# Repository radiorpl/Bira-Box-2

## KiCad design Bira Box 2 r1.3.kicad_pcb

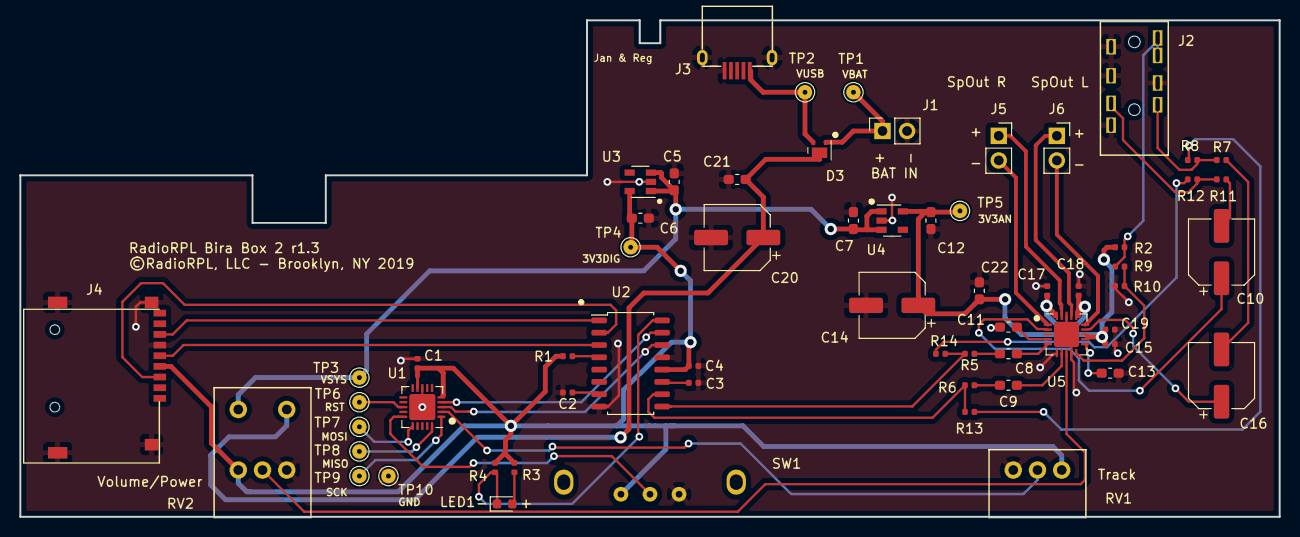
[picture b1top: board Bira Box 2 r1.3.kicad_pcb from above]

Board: 2 copper layers, 130.0 x 51.3 mm, 62 parts (1 on the bottom side), 45 nets.

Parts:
C1, C2, C3, C4, C15, C17, C18, C19: 0.1 uF; C_0402_1005Metric
C5, C6, C7, C8, C9, C12, C13: 1 uF; C_0603_1608Metric_Pad1.05x0.95mm_HandSolder
C10, C16: 220 uF; CP_Elec_6.3x5.8
C11, C21: 2.2 uF; C_0603_1608Metric_Pad1.05x0.95mm_HandSolder
C14: 100 uF; CP_Elec_6.3x5.8
C20: 22 uF; CP_Elec_6.3x5.8
C22: 10 uF; C_0603_1608Metric_Pad1.05x0.95mm_HandSolder
D3: PMEG2020CPA; HUSON-3-1EP_2x2mm_P1.3mm_EP1.1x1.6mm
J1, J5, J6: Conn_01x02_Female; PinSocket_1x02_P2.54mm_Vertical
J2: AudioJack3_SwitchTR; PJ-3930-8A
J3: USB_B_Micro; Korean-hropartsC145779
J4: Micro_SD_Card; microSD_TF01A
LED1: PLAY; LED_0603_1608Metric
R1: 22K; C_0402_1005Metric
R2: 10k; C_0402_1005Metric
R3: 2.2K; C_0402_1005Metric
R4: 10K; C_0402_1005Metric
R5, R6: 162K; C_0402_1005Metric
R7, R8, R9, R10, R11, R12, R13, R14: 0; C_0402_1005Metric
RV1: 10K; TT_PO91
RV2: 50K; TT_P091S
SW1: SW_SPDT; Alps_SSSU111400
TP1, TP2, TP3, TP4, TP5, TP6, TP7, TP8, TP9, TP10: TestPoint; TestPoint_THTPad_D2.0mm_Drill1.0mm
U1: ATTINY841A-MU; Texas_S-PVQFN-N20_EP2.7x2.7mm
U2: YX6200-16S; SOP-16_4.55x10.3mm_P1.27mm
U3, U4: MIC5504-3.3YM5; SOT-23-5
U5: PAM8019; MLF-20-1EP_4x4mm_P0.5mm_EP2.6x2.6mm

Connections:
3V3AN: C12.1, C14.1, C15.2, C17.2, C18.1, C19.2, C22.1, R2.2, TP5.1, U4.5, U5.12, U5.13, U5.16, U5.20
3V3DIG: C1.2, C4.1, C6.1, J4.4, R1.2, R3.1, R4.1, RV1.3, RV2.1, SW1.1, TP4.1, U1.5, U1.9, U2.12, U3.5
GND: C1.1, C2.2, C3.2, C4.2, C5.2, C6.2, C7.2, C11.2, C12.2, C13.2, C14.2, C15.1, C17.1, C18.2, C19.1, C20.2, C21.1, C22.2, J1.2, J2.R2, J2.RN, J2.S, J2.TN, J3.5, J3.6, J4.6, J4.9, R10.1, RV1.1, RV2.3, SW1.3, TP10.1, U1.8, U1.21, U2.8, U2.13, U3.2, U4.2, U5.6, U5.9, U5.18, U5.21
HP-SP: R9.2, R10.2, U5.10
HPLout: C16.2, R7.2
HPRout: C10.2, R11.1
LINEL: R6.2, R13.2, U2.10
LINER: R5.2, R14.1, U2.9
LoutN: J6.2, U5.15
LoutP: J6.1, U5.17
MISO: TP8.1, U1.20
MOSI: TP7.1, U1.16
unnamed: C2.1, U2.7
unnamed: C3.1, U2.11
unnamed: C8.1, U5.5
unnamed: C8.2, R5.1
unnamed: C9.1, U5.7
unnamed: C9.2, R6.1
unnamed: C10.1, U5.2
unnamed: C11.1, U5.4
unnamed: C13.1, U5.11
unnamed: C16.1, U5.14
unnamed: J2.R2N, J2.SN, R2.1, R9.1
unnamed: J2.R, R11.2, R12.2
unnamed: J2.T, R7.1, R8.1
unnamed: LED1.1, R4.2, U2.16
unnamed: LED1.2, R3.2
unnamed: R1.1, U2.4
unnamed: R12.1, R14.2
unnamed: R8.2, R13.1
unnamed: RV1.2, U1.2
unnamed: RV2.2, U5.8
RESET: TP6.1, U1.13
RoutN: J5.2, U5.1
RoutP: J5.1, U5.19
SCK: TP9.1, U1.1
SDCLK: J4.5, U2.3
SDCMD: J4.3, U2.2
SDDATA: J4.7, U2.1
Sound-Music: SW1.2, U1.15
VBAT: D3.1, J1.1, TP1.1
VSYS_IN: C20.1, C21.2, D3.3, RV2.5
VSYS_OUT: C5.1, C7.1, RV2.4, TP3.1, U3.1, U3.3, U4.1, U4.3
VUSB: D3.2, J3.1, TP2.1
mp3_TX: U1.3, U2.14

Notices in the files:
Bira Box 2 r1.3.kicad_pcb:
©RadioRPL, LLC - Brooklyn, NY 2019
